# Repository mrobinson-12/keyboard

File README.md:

# keyboard
A simple keyboard I'm making which may or may not work to learn schematics and PCB design. This was part of the keeb program at Hack Club (keeb.hackclub.com) This took me a while to make and was made using
- Kicad
- Fusion
- My Brain
All files required to make it should be here. I hope you find this useful!
## PCB Screenshot

## Schematic

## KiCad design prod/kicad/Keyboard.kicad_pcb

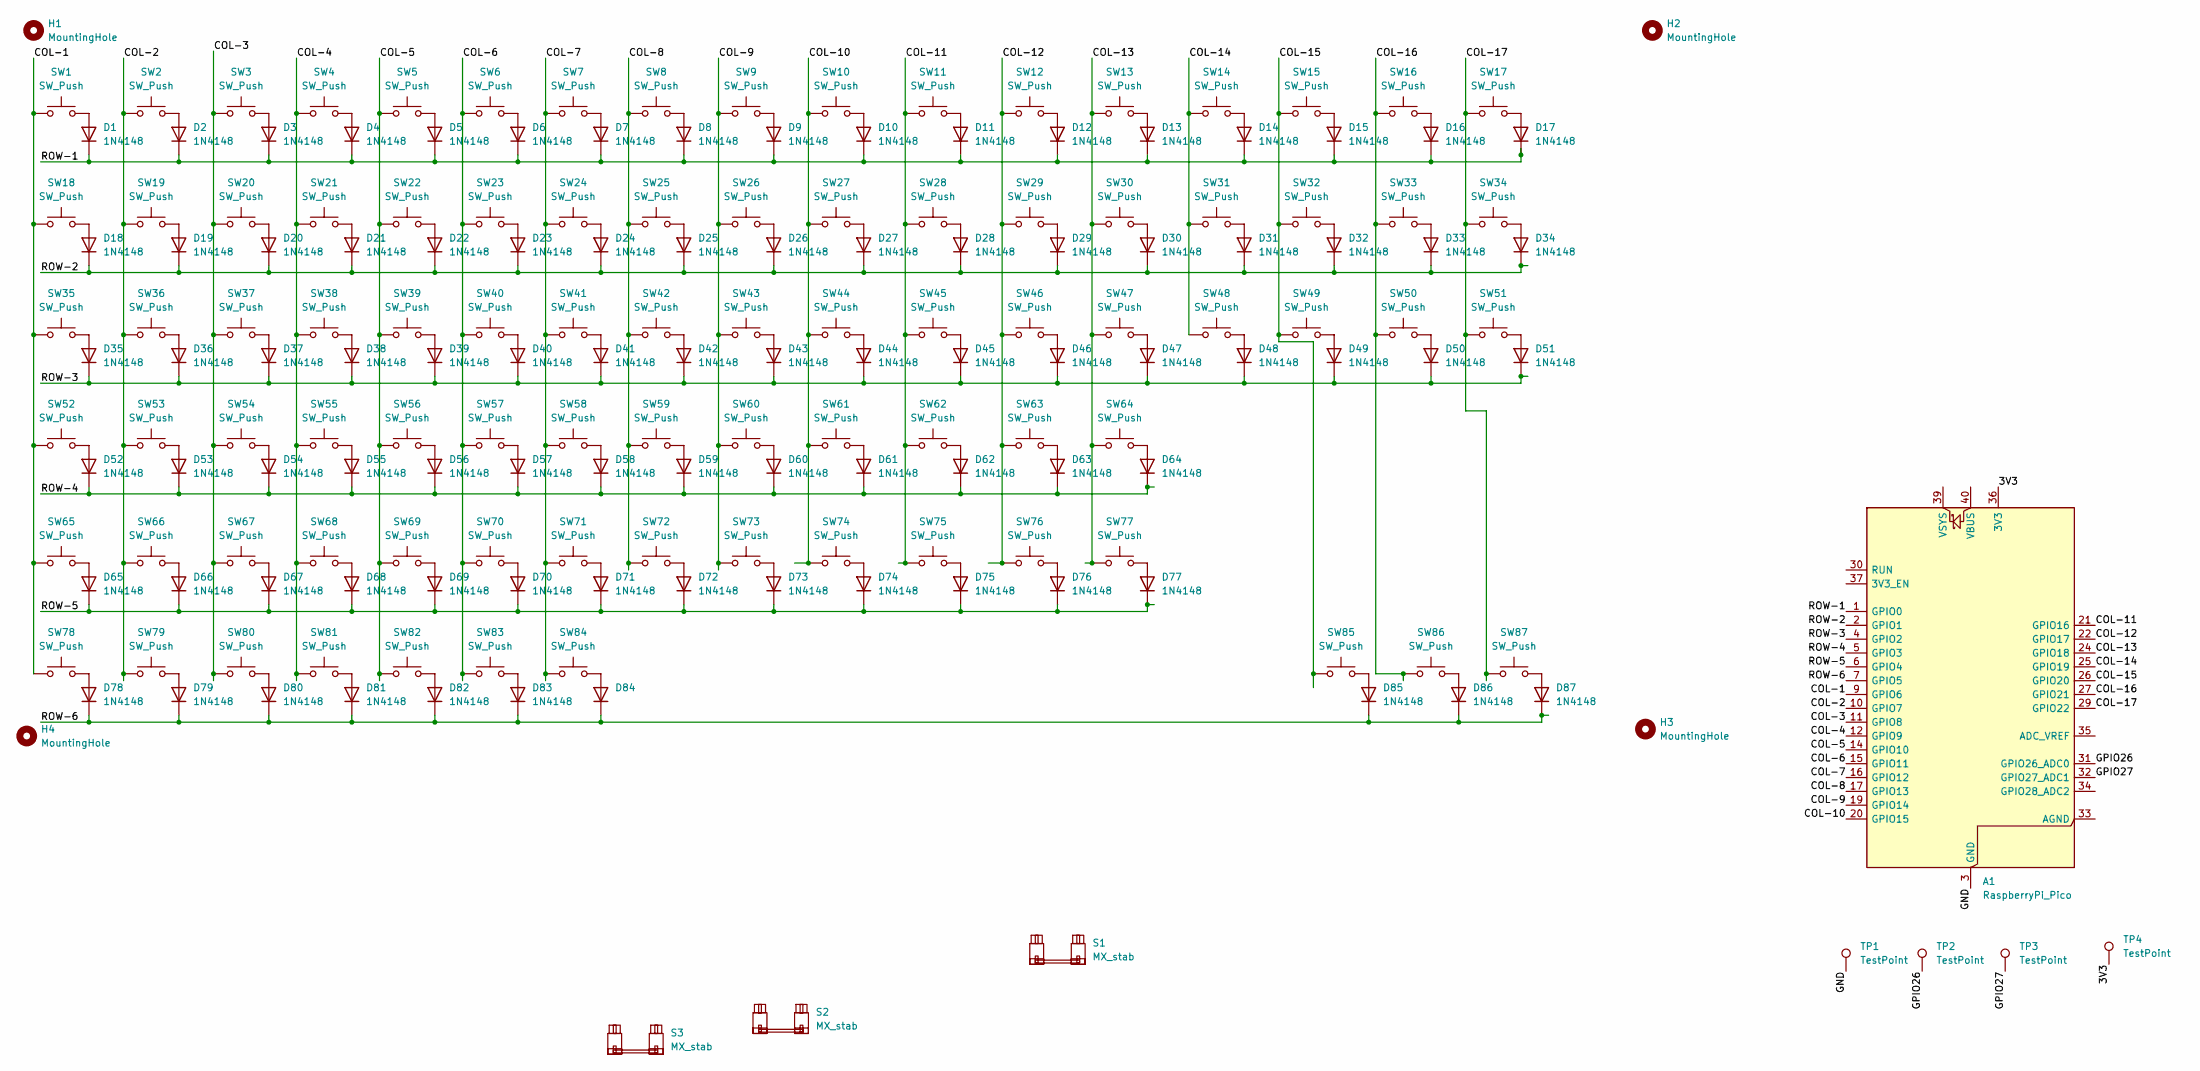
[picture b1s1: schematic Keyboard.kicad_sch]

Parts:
A1: RaspberryPi_Pico; RaspberryPi_Pico_Common_THT
D1, D2, D3, D4, D5, D6, D7, D8, D9, D10, D11, D12, D13, D14, D15, D16, D17, D18, D19, D20, D21, D22, D23, D24, D25, D26, D27, D28, D29, D30, D31, D32, D33, D34, D35, D36, D37, D38, D39, D40, D41, D42, D43, D44, D45, D46, D47, D48, D49, D50, D51, D52, D53, D54, D55, D56, D57, D58, D59, D60, D61, D62, D63, D64, D65, D66, D67, D68, D69, D70, D71, D72, D73, D74, D75, D76, D77, D78, D79, D80, D81, D82, D83, D84, D85, D86, D87: 1N4148; D_DO-35_SOD27_P7.62mm_Horizontal
H1, H2, H3, H4: MountingHole; MountingHole_3.2mm_M3
S1: MX_stab; STAB_MX_6.25u
S2, S3: MX_stab; STAB_MX_2.25u
SW1, SW2, SW3, SW4, SW5, SW6, SW7, SW8, SW9, SW10, SW11, SW12, SW13, SW14, SW15, SW16, SW17, SW18, SW19, SW20, SW21, SW22, SW23, SW24, SW25, SW26, SW27, SW28, SW29, SW30, SW32, SW33, SW34, SW35, SW36, SW37, SW38, SW39, SW40, SW41, SW42, SW43, SW44, SW45, SW46, SW47, SW48, SW49, SW50, SW51, SW52, SW53, SW54, SW55, SW56, SW57, SW58, SW59, SW60, SW61, SW62, SW63, SW64, SW65, SW66, SW67, SW68, SW69, SW70, SW71, SW72, SW73, SW74, SW75, SW76, SW77, SW78, SW79, SW80, SW81, SW82, SW83, SW84, SW85, SW86, SW87: SW_Push; SW_MX_1u
SW31: SW_Push; SW_MX_1.5u
TP1, TP2, TP3, TP4: TestPoint

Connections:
/3V3: A1.36 (3V3), TP4.1 (1_1)
/COL-1: A1.9 (GPIO6), SW1.1, SW18.1, SW35.1, SW52.1, SW65.1, SW78.1
/COL-2: A1.10 (GPIO7), SW2.1, SW19.1, SW36.1, SW53.1, SW66.1, SW79.1
/COL-3: A1.11 (GPIO8), SW3.1, SW20.1, SW37.1, SW54.1, SW67.1, SW80.1
/COL-4: A1.12 (GPIO9), SW4.1, SW21.1, SW38.1, SW55.1, SW68.1, SW81.1
/COL-5: A1.14 (GPIO10), SW5.1, SW22.1, SW39.1, SW56.1, SW69.1, SW82.1
/COL-6: A1.15 (GPIO11), SW6.1, SW23.1, SW40.1, SW57.1, SW70.1, SW83.1
/COL-7: A1.16 (GPIO12), SW7.1, SW24.1, SW41.1, SW58.1, SW71.1, SW84.1
/COL-8: A1.17 (GPIO13), SW8.1, SW25.1, SW42.1, SW59.1, SW72.1
/COL-9: A1.19 (GPIO14), SW9.1, SW26.1, SW43.1, SW60.1, SW73.1
/COL-10: A1.20 (GPIO15), SW10.1, SW27.1, SW44.1, SW61.1, SW74.1
/COL-11: A1.21 (GPIO16), SW11.1, SW28.1, SW45.1, SW62.1, SW75.1
/COL-12: A1.22 (GPIO17), SW12.1, SW29.1, SW46.1, SW63.1, SW76.1
/COL-13: A1.24 (GPIO18), SW13.1, SW30.1, SW47.1, SW64.1, SW77.1
/COL-14: A1.25 (GPIO19), SW14.1, SW31.1, SW48.1
/COL-15: A1.26 (GPIO20), SW15.1, SW32.1, SW49.1, SW85.1
/COL-16: A1.27 (GPIO21), SW16.1, SW33.1, SW50.1, SW86.1
/COL-17: A1.29 (GPIO22), SW17.1, SW34.1, SW51.1, SW87.1
/GND: A1.3 (GND), A1.8 (GND), A1.13 (GND), A1.18 (GND), A1.23 (GND), A1.28 (GND), A1.38 (GND), TP1.1 (1_1)
/GPIO26: A1.31 (GPIO26_ADC0), TP2.1 (1_1)
/GPIO27: A1.32 (GPIO27_ADC1), TP3.1 (1_1)
/ROW-1: A1.1 (GPIO0), D1.1 (K), D2.1 (K), D3.1 (K), D4.1 (K), D5.1 (K), D6.1 (K), D7.1 (K), D8.1 (K), D9.1 (K), D10.1 (K), D11.1 (K), D12.1 (K), D13.1 (K), D14.1 (K), D15.1 (K), D16.1 (K), D17.1 (K)
/ROW-2: A1.2 (GPIO1), D18.1 (K), D19.1 (K), D20.1 (K), D21.1 (K), D22.1 (K), D23.1 (K), D24.1 (K), D25.1 (K), D26.1 (K), D27.1 (K), D28.1 (K), D29.1 (K), D30.1 (K), D31.1 (K), D32.1 (K), D33.1 (K), D34.1 (K)
/ROW-3: A1.4 (GPIO2), D35.1 (K), D36.1 (K), D37.1 (K), D38.1 (K), D39.1 (K), D40.1 (K), D41.1 (K), D42.1 (K), D43.1 (K), D44.1 (K), D45.1 (K), D46.1 (K), D47.1 (K), D48.1 (K), D49.1 (K), D50.1 (K), D51.1 (K)
/ROW-4: A1.5 (GPIO3), D52.1 (K), D53.1 (K), D54.1 (K), D55.1 (K), D56.1 (K), D57.1 (K), D58.1 (K), D59.1 (K), D60.1 (K), D61.1 (K), D62.1 (K), D63.1 (K), D64.1 (K)
/ROW-5: A1.6 (GPIO4), D65.1 (K), D66.1 (K), D67.1 (K), D68.1 (K), D69.1 (K), D70.1 (K), D71.1 (K), D72.1 (K), D73.1 (K), D74.1 (K), D75.1 (K), D76.1 (K), D77.1 (K)
/ROW-6: A1.7 (GPIO5), D78.1 (K), D79.1 (K), D80.1 (K), D81.1 (K), D82.1 (K), D83.1 (K), D84.1 (K), D85.1 (K), D86.1 (K), D87.1 (K)
unnamed: D1.2 (A), SW1.2
unnamed: D2.2 (A), SW2.2
unnamed: D3.2 (A), SW3.2
unnamed: D4.2 (A), SW4.2
unnamed: D5.2 (A), SW5.2
unnamed: D6.2 (A), SW6.2
unnamed: D7.2 (A), SW7.2
unnamed: D8.2 (A), SW8.2
unnamed: D9.2 (A), SW9.2
unnamed: D10.2 (A), SW10.2
unnamed: D11.2 (A), SW11.2
unnamed: D12.2 (A), SW12.2
unnamed: D13.2 (A), SW13.2
unnamed: D14.2 (A), SW14.2
unnamed: D15.2 (A), SW15.2
unnamed: D16.2 (A), SW16.2
unnamed: D17.2 (A), SW17.2
unnamed: D18.2 (A), SW18.2
unnamed: D19.2 (A), SW19.2
unnamed: D20.2 (A), SW20.2
unnamed: D21.2 (A), SW21.2
unnamed: D22.2 (A), SW22.2
unnamed: D23.2 (A), SW23.2
unnamed: D24.2 (A), SW24.2
unnamed: D25.2 (A), SW25.2
unnamed: D26.2 (A), SW26.2
unnamed: D27.2 (A), SW27.2
unnamed: D28.2 (A), SW28.2
unnamed: D29.2 (A), SW29.2
unnamed: D30.2 (A), SW30.2
unnamed: D31.2 (A), SW31.2
unnamed: D32.2 (A), SW32.2
unnamed: D33.2 (A), SW33.2
unnamed: D34.2 (A), SW34.2
unnamed: D35.2 (A), SW35.2
unnamed: D36.2 (A), SW36.2
unnamed: D37.2 (A), SW37.2
unnamed: D38.2 (A), SW38.2
unnamed: D39.2 (A), SW39.2
unnamed: D40.2 (A), SW40.2
unnamed: D41.2 (A), SW41.2
unnamed: D42.2 (A), SW42.2
unnamed: D43.2 (A), SW43.2
unnamed: D44.2 (A), SW44.2
unnamed: D45.2 (A), SW45.2
unnamed: D46.2 (A), SW46.2
unnamed: D47.2 (A), SW47.2
unnamed: D48.2 (A), SW48.2
unnamed: D49.2 (A), SW49.2
unnamed: D50.2 (A), SW50.2
unnamed: D51.2 (A), SW51.2
unnamed: D52.2 (A), SW52.2
unnamed: D53.2 (A), SW53.2
unnamed: D54.2 (A), SW54.2
unnamed: D55.2 (A), SW55.2
unnamed: D56.2 (A), SW56.2
unnamed: D57.2 (A), SW57.2
unnamed: D58.2 (A), SW58.2
unnamed: D59.2 (A), SW59.2
unnamed: D60.2 (A), SW60.2
unnamed: D61.2 (A), SW61.2
unnamed: D62.2 (A), SW62.2
unnamed: D63.2 (A), SW63.2
unnamed: D64.2 (A), SW64.2
unnamed: D65.2 (A), SW65.2
unnamed: D66.2 (A), SW66.2
unnamed: D67.2 (A), SW67.2
unnamed: D68.2 (A), SW68.2
unnamed: D69.2 (A), SW69.2
unnamed: D70.2 (A), SW70.2
unnamed: D71.2 (A), SW71.2
unnamed: D72.2 (A), SW72.2
unnamed: D73.2 (A), SW73.2
unnamed: D74.2 (A), SW74.2
unnamed: D75.2 (A), SW75.2
unnamed: D76.2 (A), SW76.2
unnamed: D77.2 (A), SW77.2
unnamed: D78.2 (A), SW78.2
unnamed: D79.2 (A), SW79.2
unnamed: D80.2 (A), SW80.2
unnamed: D81.2 (A), SW81.2
unnamed: D82.2 (A), SW82.2
unnamed: D83.2 (A), SW83.2
unnamed: D84.2 (A), SW84.2
unnamed: D85.2 (A), SW85.2
unnamed: D86.2 (A), SW86.2
unnamed: D87.2 (A), SW87.2

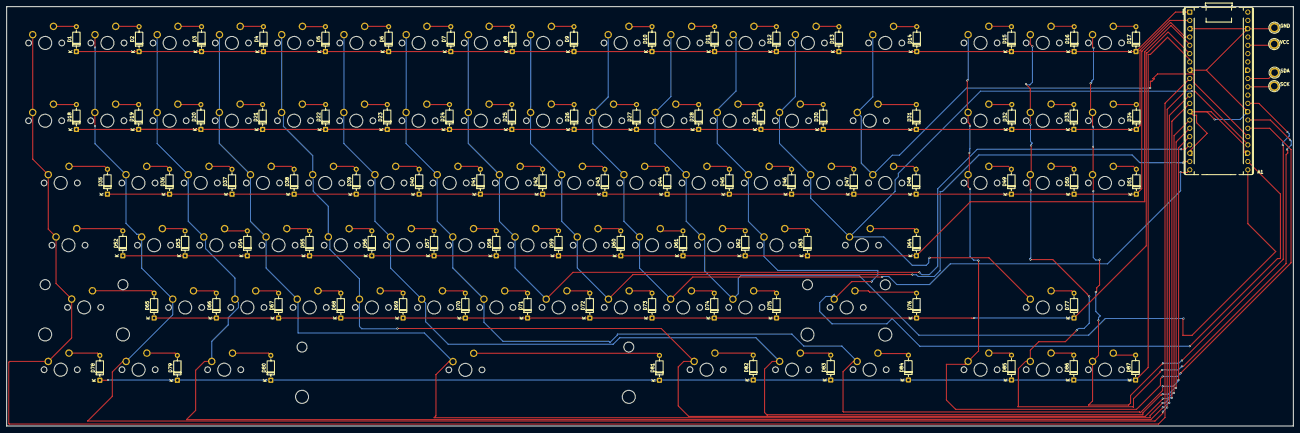
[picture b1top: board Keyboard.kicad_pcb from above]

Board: 2 copper layers, 393.8 x 128.4 mm, 182 parts (0 on the bottom side), 114 nets.

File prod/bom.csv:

"Id";"Designator";"Footprint";"Quantity";"Designation";"Supplier and ref";
1;"A1";"RaspberryPi_Pico_Common_THT";1;"RaspberryPi_Pico";;;
2;"D1, D2, D3, D4, D5, D6, D7, D8, D9, D10, D11, D12, D13, D14, D15, D16, D17, D18, D19, D20, D21, D22, D23, D24, D25, D26, D27, D28, D29, D30, D31, D32, D33, D34, D35, D36, D37, D38, D39, D40, D41, D42, D43, D44, D45, D46, D47, D48, D49, D50, D51, D52, D53, D54, D55, D56, D57, D58, D59, D60, D61, D62, D63, D64, D65, D66, D67, D68, D69, D70, D71, D72, D73, D74, D75, D76, D77, D78, D79, D80, D81, D82, D83, D84, D85, D86, D87";"D_DO-35_SOD27_P7.62mm_Horizontal";87;"1N4148";;;
3;"S3";"STAB_MX_6.25u";1;"MX_stab";;;
4;"SW31, SW35, SW80, SW82";"SW_MX_1.5u";4;"SW_Push";;;
5;"SW78, SW79, SW83, SW84";"SW_MX_1.25u";4;"SW_Push";;;
